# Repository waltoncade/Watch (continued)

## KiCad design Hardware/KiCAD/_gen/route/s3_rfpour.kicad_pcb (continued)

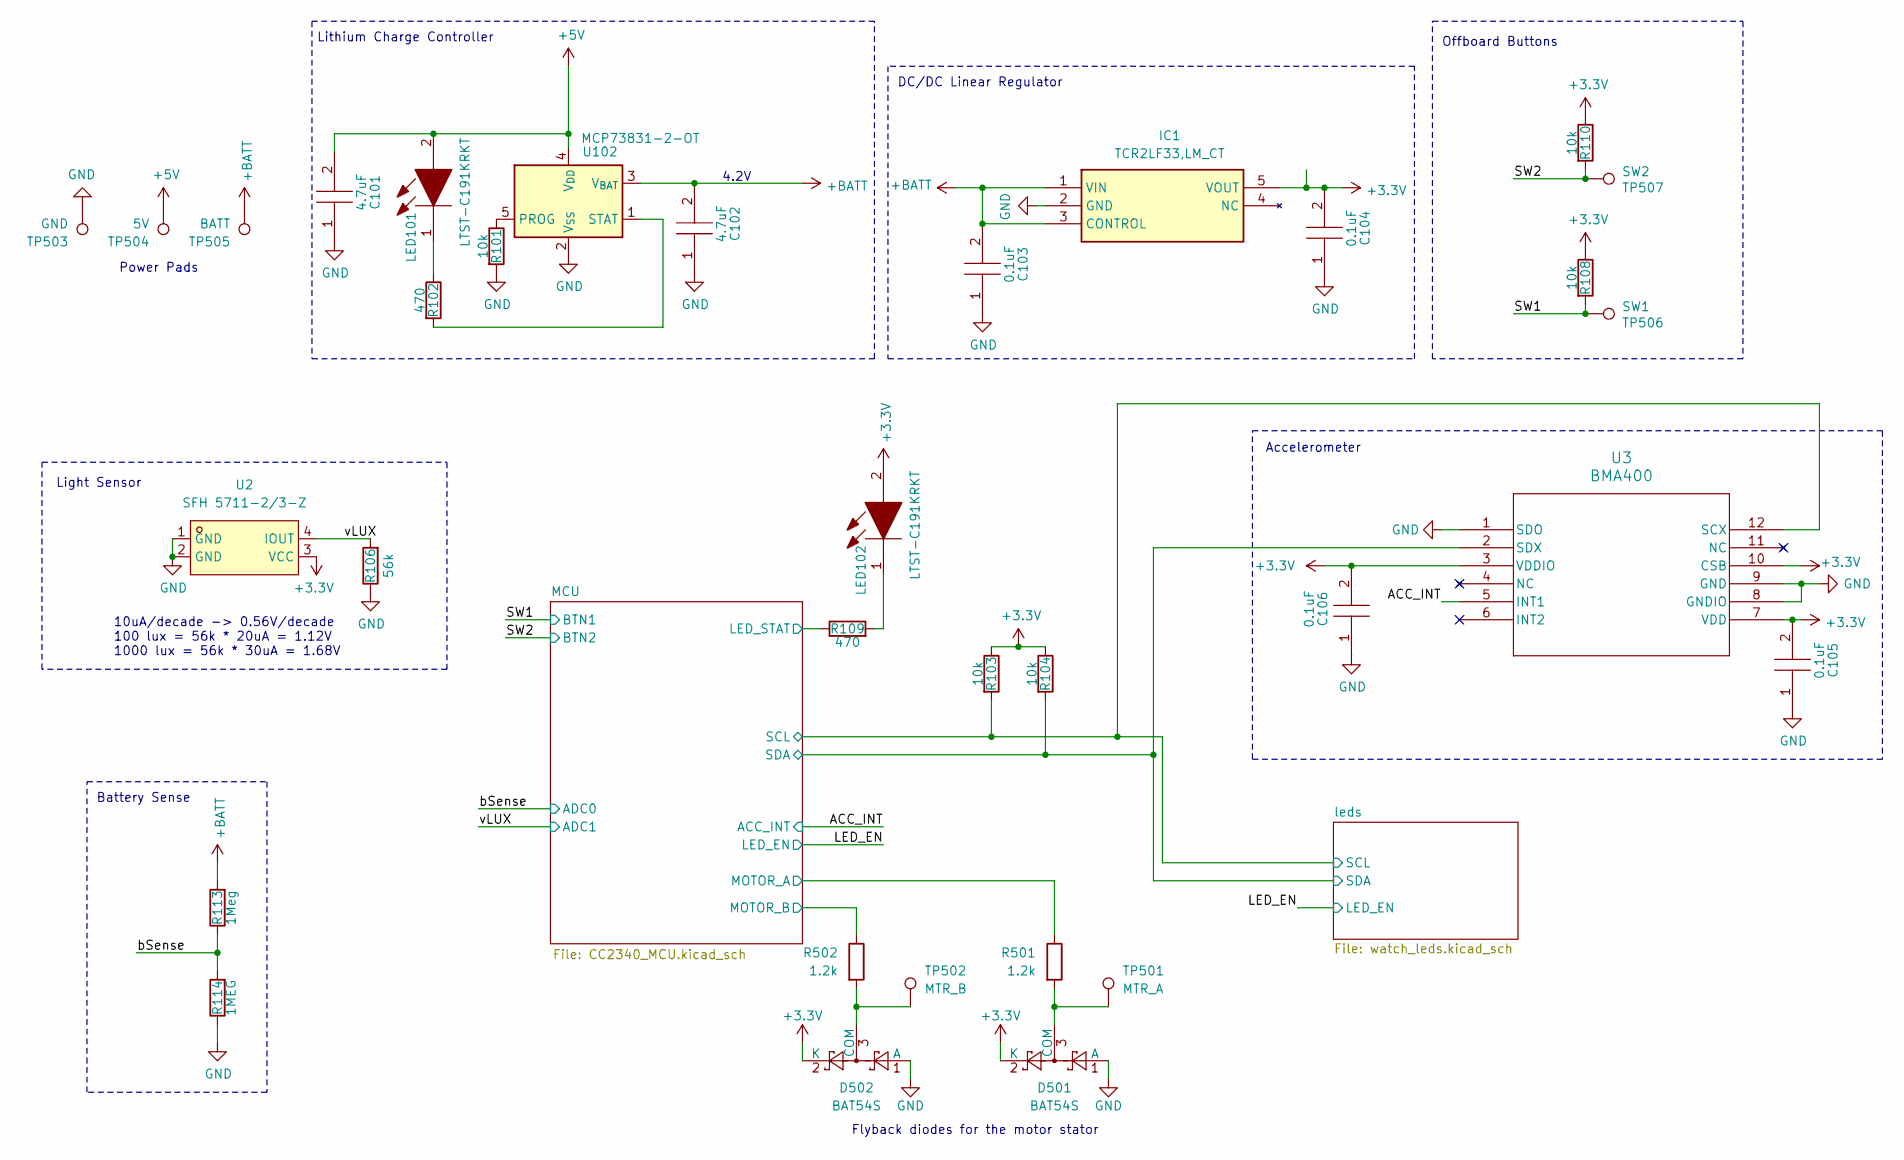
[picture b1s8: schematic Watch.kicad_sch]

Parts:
C101, C102: 4.7uF; CAPC1005X55N; Manufacturer_Part_Number CL05A104KA5NNNC; Mouser Part Number 187-CL05A104KA5NNNC
C103, C104, C105, C106: 0.1uF; CAPC1005X55N; Manufacturer_Part_Number CL05A104KA5NNNC; Mouser Part Number 187-CL05A104KA5NNNC
D501, D502: BAT54S; SOT-23
IC1: TCR2LF33,LM_CT; TCR2LF33LMCT; Manufacturer_Part_Number TCR2LF33,LM(CT; Mouser Part Number 757-TCR2LF33LMCT
LED101, LED102: LTST-C191KRKT; LEDC1608X55N; Manufacturer_Part_Number LTST-C191KRKT; Mouser Part Number 859-LTST-C191KRKT
R101, R103, R104, R108, R110: 10k; R_0402_1005Metric
R102, R109: 470; R_0402_1005Metric
R106: 56k; R_0402_1005Metric
R113: 1Meg; R_0402_1005Metric
R114: 1MEG; R_0402_1005Metric
R501, R502: 1.2k; R_0402_1005Metric
TP501: MTR_A; TestPoint_Pad_1.5x1.5mm
TP502: MTR_B; TestPoint_Pad_1.5x1.5mm
TP503: GND; TestPoint_Pad_1.5x1.5mm
TP504: 5V; TestPoint_Pad_1.5x1.5mm
TP505: BATT; TestPoint_Pad_1.5x1.5mm
TP506: SW1; TestPoint_Pad_1.5x1.5mm
TP507: SW2; TestPoint_Pad_1.5x1.5mm
U2: SFH 5711-2/3-Z; LED-SMD_4P-L2.8-W2.2-FD; MPN SFH 5711-2/3-Z; LCSC Part C2655106
U3: BMA400; QFN_BMA400_BOS-L
U102: MCP73831-2-OT; SOT-23-5

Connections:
+3.3V: C104.2, C105.2, C106.2, D501.2 (K), D502.2 (K), IC1.5 (VOUT), LED102.2, R103.1, R104.1, R108.1, R110.1, U2.3 (VCC), U3.3 (VDDIO), U3.7 (VDD), U3.10 (CSB); also elsewhere on the board
+5V: C101.2, LED101.2, TP504.1 (1_1), U102.4 (V_{DD})
+BATT: C102.2, C103.2, IC1.1 (VIN), IC1.3 (CONTROL), R113.2, TP505.1 (1_1), U102.3 (V_{BAT})
/ACC_INT: U3.5 (INT1); also elsewhere on the board
/MCU/LED_STAT: R109.1; also elsewhere on the board
/MCU/MOTOR_A: R501.1; also elsewhere on the board
/MCU/MOTOR_B: R502.1; also elsewhere on the board
/SW1: R108.2, TP506.1 (1_1); also elsewhere on the board
/SW2: R110.2, TP507.1 (1_1); also elsewhere on the board
/bSense: R113.1, R114.2; also elsewhere on the board
/leds/SCL: R103.2, U3.12 (SCX); also elsewhere on the board
/leds/SDA: R104.2, U3.2 (SDX); also elsewhere on the board
/vLUX: R106.2, U2.4 (IOUT); also elsewhere on the board
GND: C101.1, C102.1, C103.1, C104.1, C105.1, C106.1, D501.1 (A), D502.1 (A), IC1.2 (GND), R101.2, R106.1, R114.1, TP503.1 (1_1), U2.1 (GND), U2.2 (GND), U3.1 (SDO), U3.8 (GNDIO), U3.9 (GND), U102.2 (V_{SS}); also elsewhere on the board
unnamed: D501.3 (COM), R501.2, TP501.1 (1_1)
unnamed: D502.3 (COM), R502.2, TP502.1 (1_1)
unnamed: LED101.1, R102.1
unnamed: LED102.1, R109.2
unnamed: R101.1, U102.5 (PROG)
unnamed: R102.2, U102.1 (STAT)

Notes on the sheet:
Power Pads
Flyback diodes for the motor stator
4.2V
Battery Sense
Lithium Charge Controller
Offboard Buttons
DC/DC Linear Regulator
Light Sensor
Accelerometer
10uA/decade -> 0.56V/decade 100 lux = 56k * 20uA = 1.12V 1000 lux = 56k * 30uA = 1.68V

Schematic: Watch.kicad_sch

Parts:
C101, C102: 4.7uF; CAPC1005X55N; Manufacturer_Part_Number CL05A104KA5NNNC; Mouser Part Number 187-CL05A104KA5NNNC
C103, C104, C105, C106: 0.1uF; CAPC1005X55N; Manufacturer_Part_Number CL05A104KA5NNNC; Mouser Part Number 187-CL05A104KA5NNNC
D501, D502: BAT54S; SOT-23
IC1: TCR2LF33,LM_CT; TCR2LF33LMCT; Manufacturer_Part_Number TCR2LF33,LM(CT; Mouser Part Number 757-TCR2LF33LMCT
LED101, LED102: LTST-C191KRKT; LEDC1608X55N; Manufacturer_Part_Number LTST-C191KRKT; Mouser Part Number 859-LTST-C191KRKT
R101, R103, R104, R108, R110: 10k; R_0402_1005Metric
R102, R109: 470; R_0402_1005Metric
R106: 56k; R_0402_1005Metric
R113: 1Meg; R_0402_1005Metric
R114: 1MEG; R_0402_1005Metric
R501, R502: 1.2k; R_0402_1005Metric
TP501: MTR_A; TestPoint_Pad_D1.5mm
TP502: MTR_B; TestPoint_Pad_D1.5mm
TP503: GND; TestPoint_Pad_D1.5mm
TP504: 5V; TestPoint_Pad_D1.5mm
TP505: BATT; TestPoint_Pad_D1.5mm
TP506: SW1; TestPoint_Pad_D1.5mm
TP507: SW2; TestPoint_Pad_D1.5mm
U2: SFH 5711-2/3-Z; LED-SMD_4P-L2.8-W2.2-FD; MPN SFH 5711-2/3-Z; LCSC Part C2655106
U3: BMA400; QFN_BMA400_BOS-L
U102: MCP73831-2-OT; SOT-23-5

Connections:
+3.3V: C104.2, C105.2, C106.2, D501.2 (K), D502.2 (K), IC1.5 (VOUT), LED102.2, R103.1, R104.1, R108.1, R110.1, U2.3 (VCC), U3.3 (VDDIO), U3.7 (VDD), U3.10 (CSB); also elsewhere on the board
+5V: C101.2, LED101.2, TP504.1 (1_1), U102.4 (V_{DD})
+BATT: C102.2, C103.2, IC1.1 (VIN), IC1.3 (CONTROL), R113.2, TP505.1 (1_1), U102.3 (V_{BAT})
/ACC_INT: U3.5 (INT1); also elsewhere on the board
/MCU/LED_STAT: R109.1; also elsewhere on the board
/MCU/MOTOR_A: R501.1; also elsewhere on the board
/MCU/MOTOR_B: R502.1; also elsewhere on the board
/SW1: R108.2, TP506.1 (1_1); also elsewhere on the board
/SW2: R110.2, TP507.1 (1_1); also elsewhere on the board
/bSense: R113.1, R114.2; also elsewhere on the board
/leds/SCL: R103.2, U3.12 (SCX); also elsewhere on the board
/leds/SDA: R104.2, U3.2 (SDX); also elsewhere on the board
/vLUX: R106.2, U2.4 (IOUT); also elsewhere on the board
GND: C101.1, C102.1, C103.1, C104.1, C105.1, C106.1, D501.1 (A), D502.1 (A), IC1.2 (GND), R101.2, R106.1, R114.1, TP503.1 (1_1), U2.1 (GND), U2.2 (GND), U3.1 (SDO), U3.8 (GNDIO), U3.9 (GND), U102.2 (V_{SS}); also elsewhere on the board
unnamed: D501.3 (COM), R501.2, TP501.1 (1_1)
unnamed: D502.3 (COM), R502.2, TP502.1 (1_1)
unnamed: LED101.1, R102.1
unnamed: LED102.1, R109.2
unnamed: R101.1, U102.5 (PROG)
unnamed: R102.2, U102.1 (STAT)

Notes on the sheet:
Power Pads
Flyback diodes for the motor stator
4.2V
Battery Sense
Lithium Charge Controller
Offboard Buttons
DC/DC Linear Regulator
Light Sensor
Accelerometer
10uA/decade -> 0.56V/decade 100 lux = 56k * 20uA = 1.12V 1000 lux = 56k * 30uA = 1.68V

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
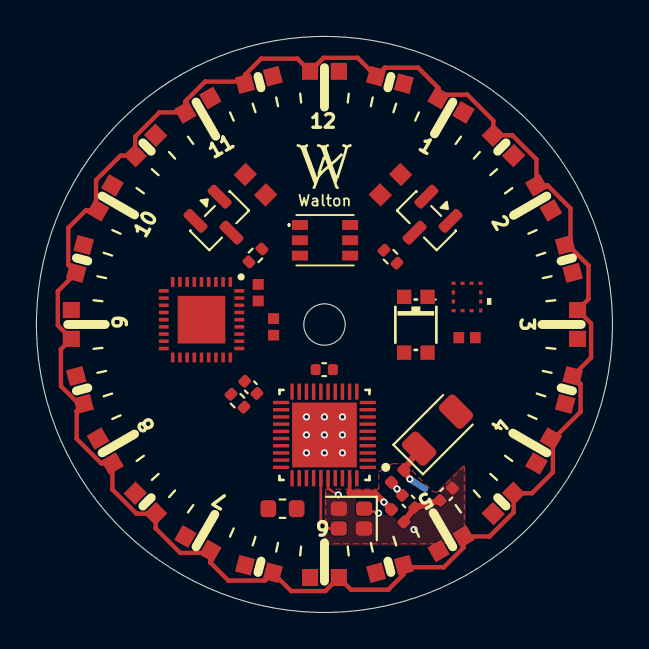
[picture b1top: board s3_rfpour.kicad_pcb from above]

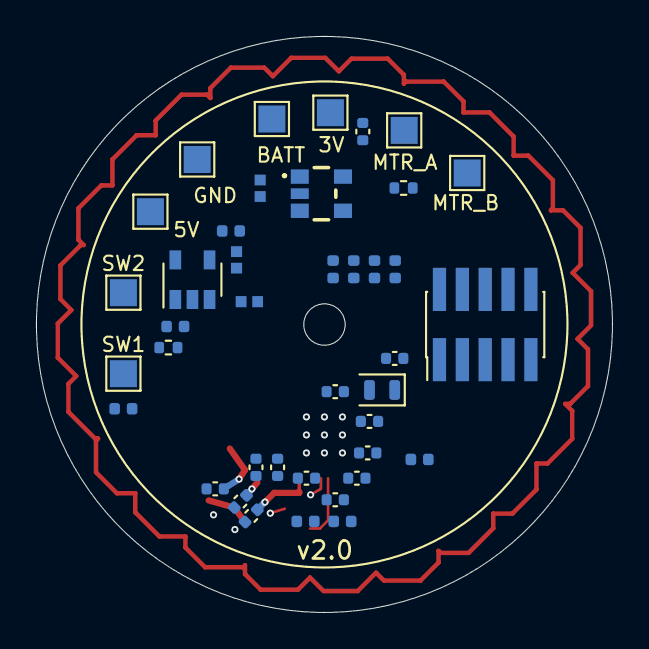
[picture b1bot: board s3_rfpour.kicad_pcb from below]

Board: 4 copper layers, 32.0 x 32.0 mm, 90 parts (40 on the bottom side), 63 nets.

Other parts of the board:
H1: Hand shaft 2.3mm NPTH; NPTH_2.0mm_HandShaft
LOGO1: W_Logo
TP508: 3V; TestPoint_Pad_1.5x1.5mm

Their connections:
+3.3V: TP508.1; also elsewhere on the board
